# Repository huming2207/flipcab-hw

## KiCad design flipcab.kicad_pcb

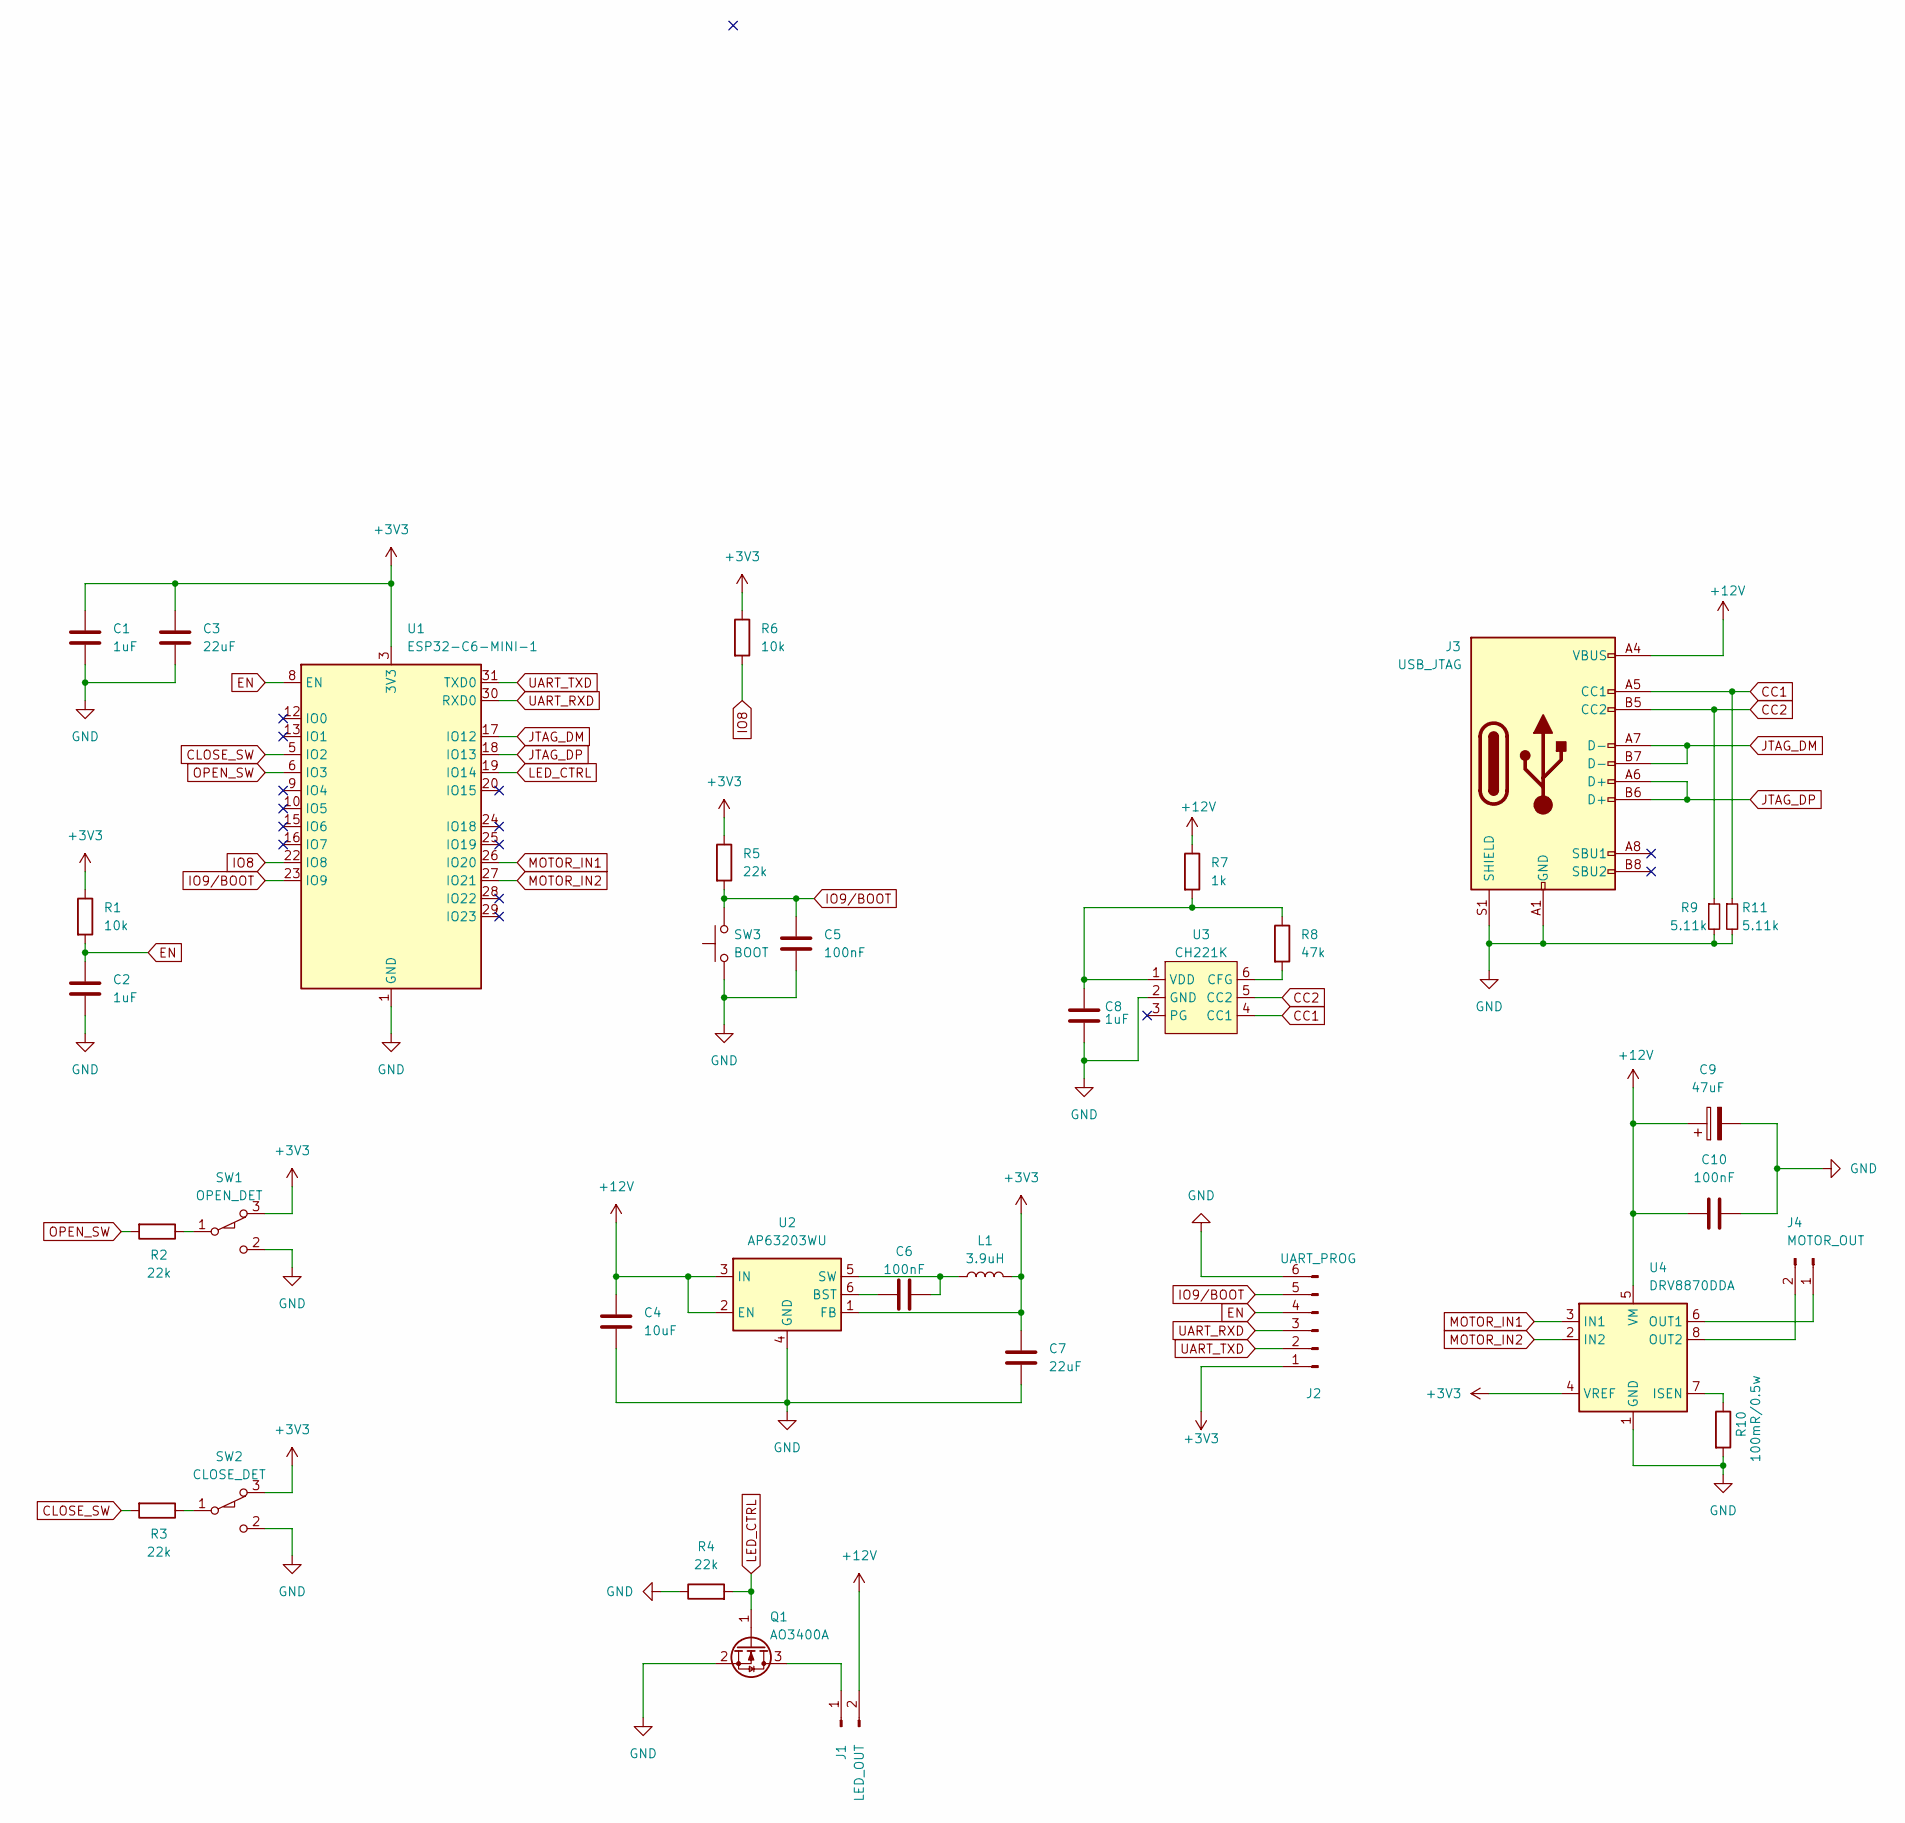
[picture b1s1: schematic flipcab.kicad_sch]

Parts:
C1, C2: 1uF; C_0402_1005Metric; LCSC C15525
C3: 22uF; C_0603_1608Metric; LCSC C59461
C4: 10uF; C_0603_1608Metric
C5: 100nF; C_0402_1005Metric; LCSC C1525
C6: 100nF; C_0402_1005Metric
C7: 22uF; C_0603_1608Metric
C8: 1uF; C_0603_1608Metric
C9: 47uF; CP_EIA-7343-31_Kemet-D
C10: 100nF; C_0402_1005Metric; LCSC C1554
J1: LED_OUT; PinHeader_1x02_P2.54mm_Vertical
J2: UART_PROG; PinHeader_1x06_P1.27mm_Vertical
J3: USB_JTAG; USB_C_Receptacle_HRO_TYPE-C-31-M-12; LCSC C709357
J4: MOTOR_OUT; PinHeader_1x02_P2.54mm_Vertical
L1: 3.9uH; L_Changjiang_FNR3015S
Q1: AO3400A; SOT-23
R1, R6: 10k; R_0402_1005Metric; LCSC C25744
R2, R3, R4, R5: 22k; R_0402_1005Metric; LCSC C25744
R7: 1k; R_0402_1005Metric
R8: 47k; R_0402_1005Metric
R9, R11: 5.11k; R_0402_1005Metric; LCSC C25905
R10: 100mR/0.5w; R_1206_3216Metric; LCSC C25744
SW1: OPEN_DET; SW_XKB_DM1-16UP-1
SW2: CLOSE_DET; SW_XKB_DM1-16UP-1
SW3: BOOT; SW_Push_1P1T_XKB_TS-1187A; LCSC C318884
U1: ESP32-C6-MINI-1; LCSC C5736265
U2: AP63203WU; TSOT-23-6
U3: CH221K; SOT-23-6
U4: DRV8870DDA; Texas_HTSOP-8-1EP_3.9x4.9mm_P1.27mm_EP2.95x4.9mm_Mask2.4x3.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

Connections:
+3V3: C1.1, C3.1, C7.1, J2.1, L1.2, R1.1, R5.1, R6.1, SW1.3 (C), SW2.3 (C), U1.3 (3V3), U2.1 (FB), U4.4 (VREF)
+12V: C4.1, C9.1, C10.2, J1.2, J3.A4 (VBUS), J3.A9 (VBUS), J3.B4 (VBUS), J3.B9 (VBUS), R7.1, U2.2 (EN), U2.3 (IN), U4.5 (VM)
CC1: J3.A5 (CC1), R11.1, U3.4 (CC1)
CC2: J3.B5 (CC2), R9.1, U3.5 (CC2)
CLOSE_SW: R3.2, U1.5 (IO2)
EN: C2.1, J2.4, R1.2, U1.8 (EN)
GND: C1.2, C2.2, C3.2, C4.2, C5.2, C7.2, C8.2, C9.2, C10.1, J2.6, J3.A1 (GND), J3.A12 (GND), J3.B1 (GND), J3.B12 (GND), J3.S1 (SHIELD), Q1.2 (S), R4.1, R9.2, R10.2, R11.2, SW1.2 (B), SW2.2 (B), SW3.1, U1.1 (GND), U1.2 (GND), U1.11 (GND), U1.14 (GND), U1.36 (GND), U1.37 (GND), U1.38 (GND), U1.39 (GND), U1.40 (GND), U1.41 (GND), U1.42 (GND), U1.43 (GND), U1.44 (GND), U1.45 (GND), U1.46 (GND), U1.47 (GND), U1.48 (GND), U1.49 (GND), U1.50 (GND), U1.51 (GND), U1.52 (GND), U1.53 (GND), U2.4 (GND), U3.2 (GND), U4.1 (GND), U4.9 (GND)
IO8: R6.2, U1.22 (IO8)
IO9/BOOT: C5.1, J2.5, R5.2, SW3.2, U1.23 (IO9)
JTAG_DM: J3.A7 (D-), J3.B7 (D-), U1.17 (IO12)
JTAG_DP: J3.A6 (D+), J3.B6 (D+), U1.18 (IO13)
LED_CTRL: Q1.1 (G), R4.2, U1.19 (IO14)
MOTOR_IN1: U1.26 (IO20), U4.3 (IN1)
MOTOR_IN2: U1.27 (IO21), U4.2 (IN2)
unnamed: J1.1, Q1.3 (D)
unnamed: J4.1, U4.6 (OUT1)
unnamed: J4.2, U4.8 (OUT2)
unnamed: R2.1, SW1.1 (A)
unnamed: R3.1, SW2.1 (A)
unnamed: C6.1, U2.6 (BST)
unnamed: C6.2, L1.1, U2.5 (SW)
unnamed: R8.2, U3.6 (CFG)
unnamed: C8.1, R7.2, R8.1, U3.1 (VDD)
unnamed: R10.1, U4.7 (ISEN)
OPEN_SW: R2.2, U1.6 (IO3)
UART_RXD: J2.3, U1.30 (RXD0)
UART_TXD: J2.2, U1.31 (TXD0)

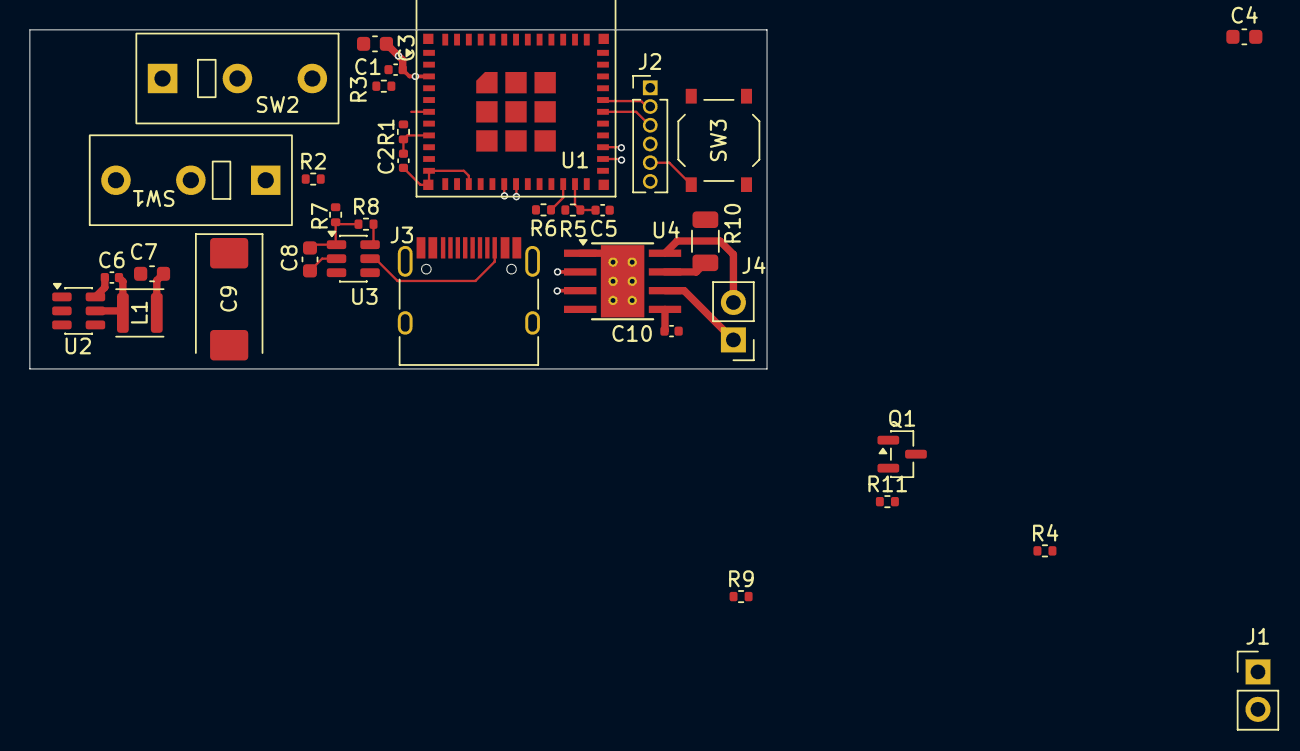
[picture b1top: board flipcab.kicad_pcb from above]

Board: 4 copper layers, 50.0 x 23.0 mm, 34 parts (0 on the bottom side), 27 nets.

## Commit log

2026-02-12 Init
2026-02-15 rev1: finish schmetic
2026-02-16 rev1: sync change
2026-02-26 rev1: send off to JLC
